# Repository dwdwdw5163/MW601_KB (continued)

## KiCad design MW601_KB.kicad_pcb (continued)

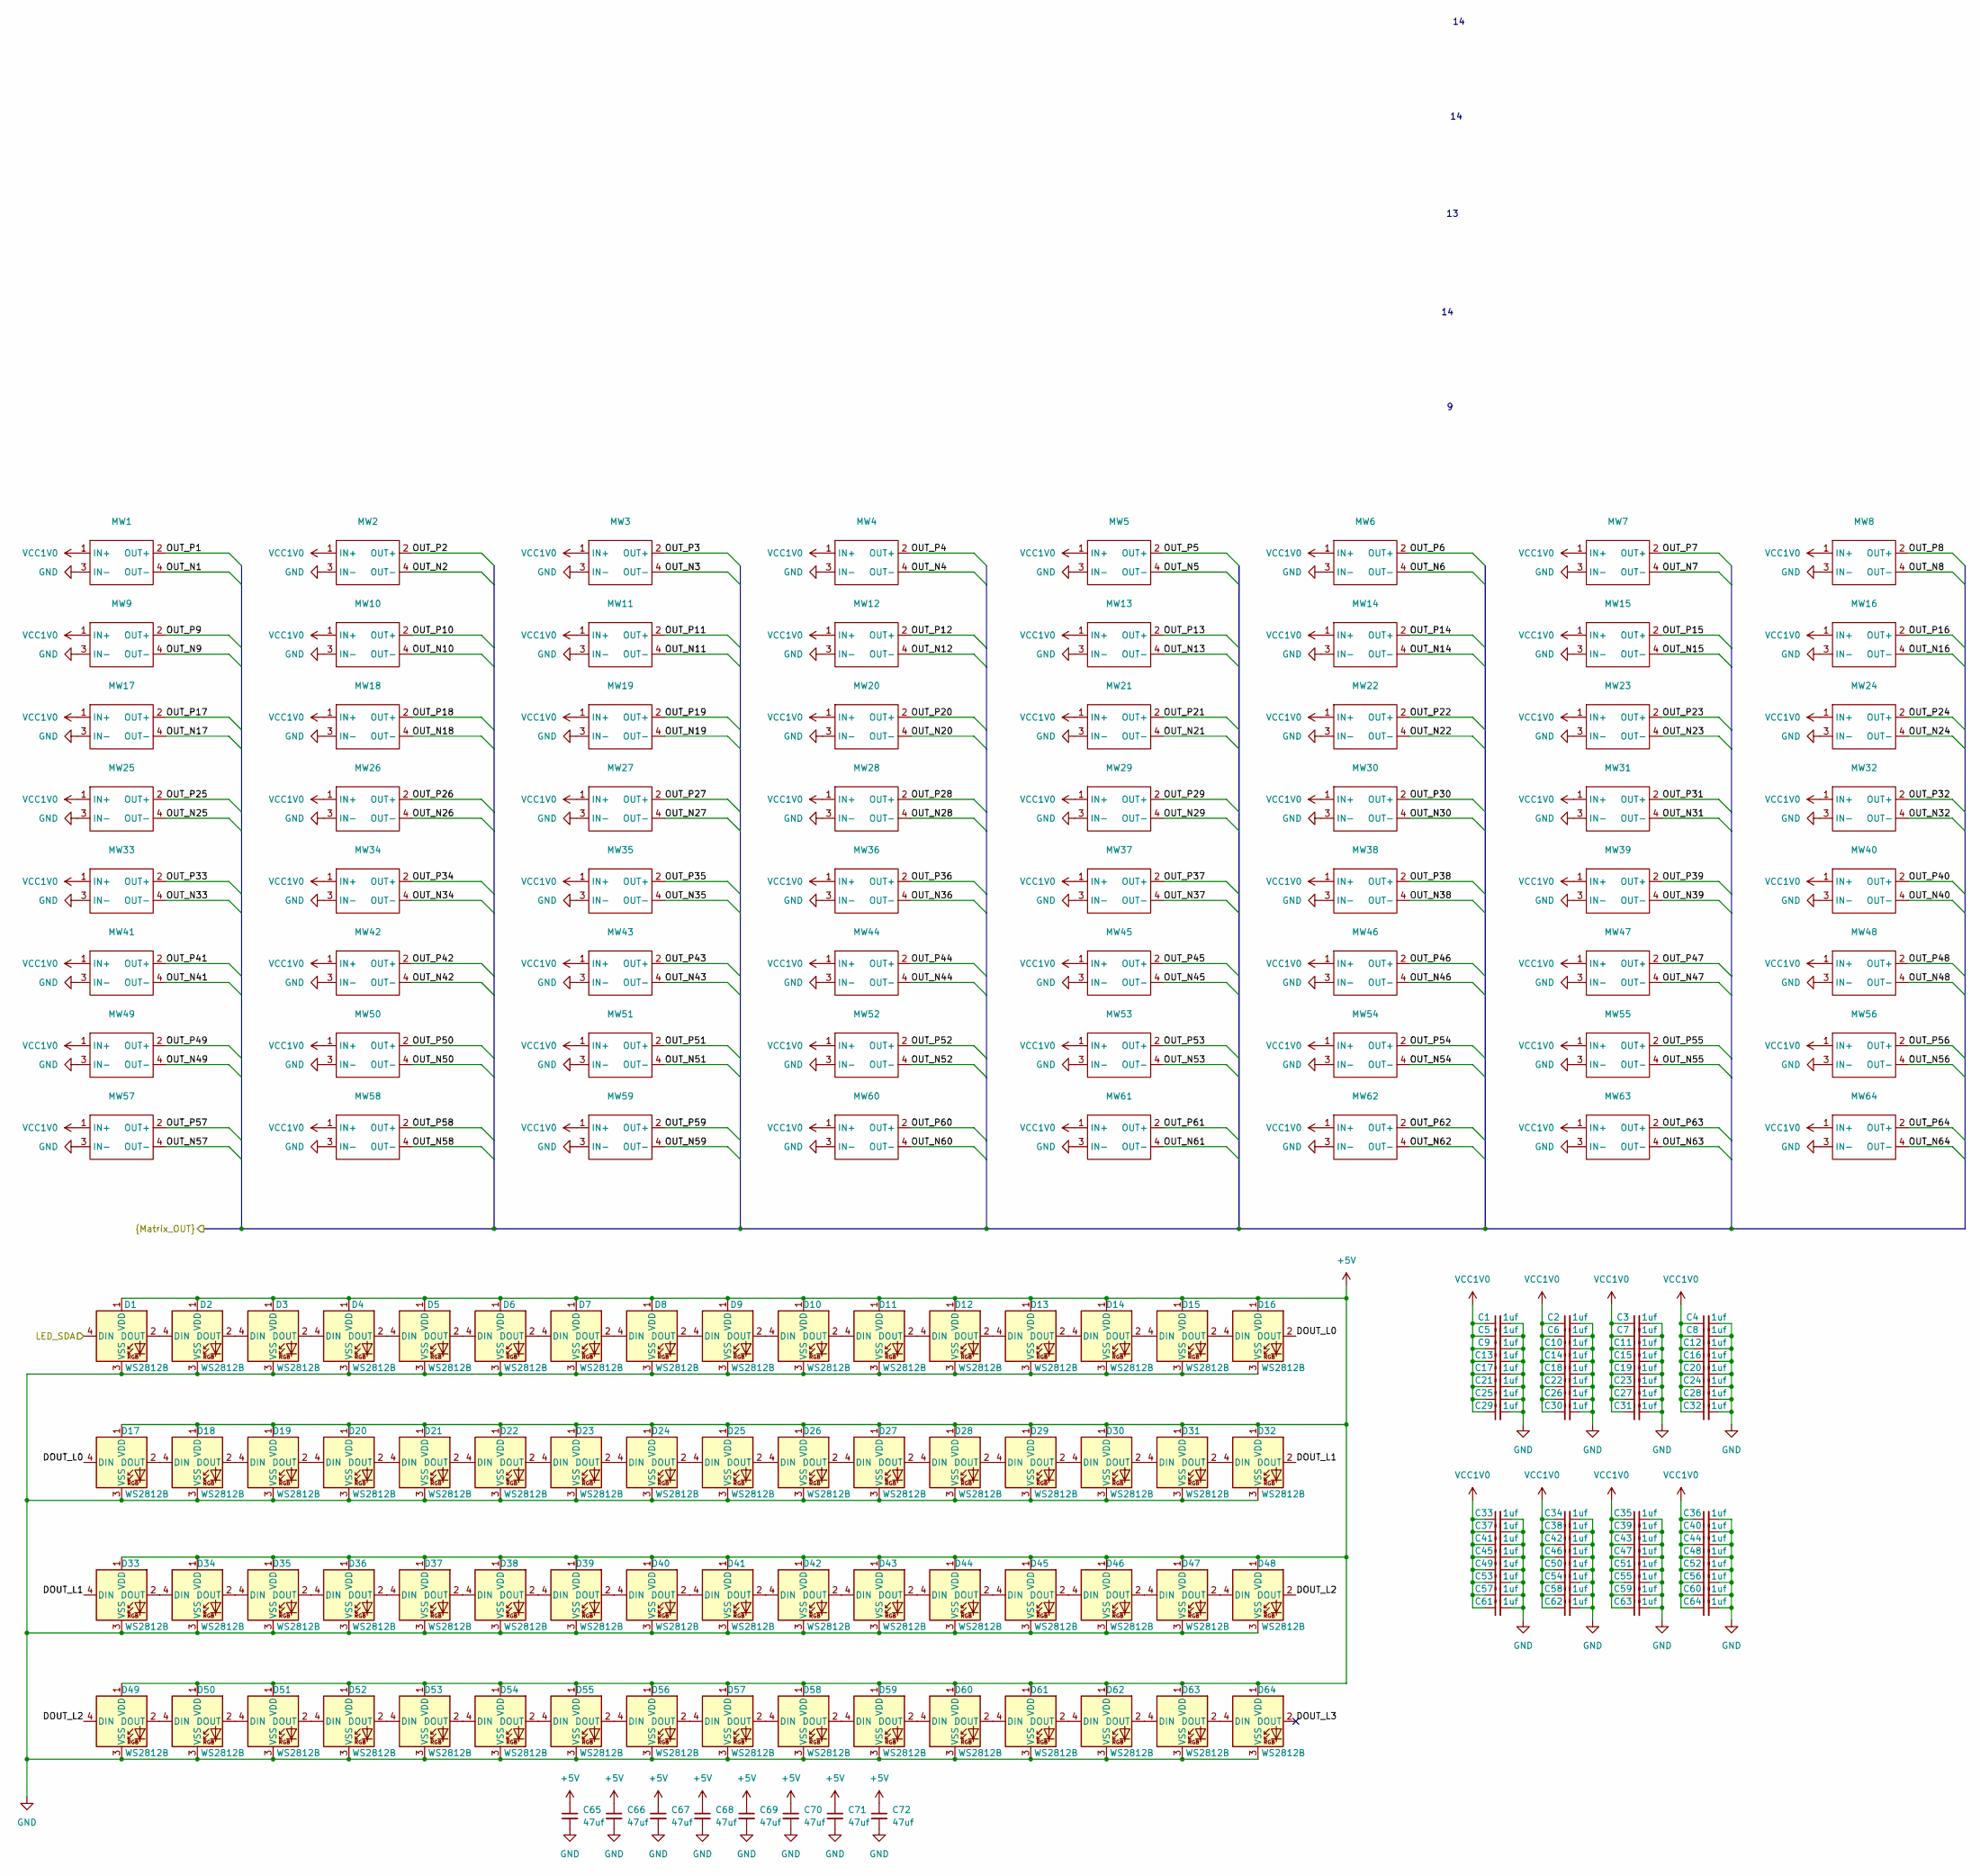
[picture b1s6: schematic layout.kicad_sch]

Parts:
C1, C2, C3, C4, C5, C6, C7, C8, C9, C10, C11, C12, C13, C14, C15, C16, C17, C18, C19, C20, C21, C22, C23, C24, C25, C26, C27, C28, C29, C30, C31, C32, C33, C34, C35, C36, C37, C38, C39, C40, C41, C42, C43, C44, C45, C46, C47, C48, C49, C50, C51, C52, C53, C54, C55, C56, C57, C58, C59, C60, C61, C62, C63, C64: 1uf; C_0603_1608Metric
C65, C66, C67, C68, C69, C70, C71, C72: 47uf; C_0805_2012Metric
D1, D2, D3, D4, D5, D6, D7, D8, D9, D10, D11, D12, D13, D14, D15, D16, D17, D18, D19, D20, D21, D22, D23, D24, D25, D26, D27, D28, D29, D30, D31, D32, D33, D34, D35, D36, D37, D38, D39, D40, D41, D42, D43, D44, D45, D46, D47, D48, D49, D50, D51, D52, D53, D54, D55, D56, D57, D58, D59, D60, D61, D62, D63, D64: WS2812B; WS2812B反贴
MW1, MW2, MW3, MW4, MW5, MW6, MW7, MW8, MW9, MW10, MW11, MW12, MW13, MW14, MW15, MW16, MW17, MW18, MW19, MW20, MW21, MW22, MW23, MW24, MW25, MW26, MW27, MW28, MW29, MW30, MW31, MW32, MW33, MW34, MW35, MW36, MW37, MW38, MW39, MW40, MW41, MW42, MW43, MW44, MW45, MW46, MW47, MW48, MW49, MW50, MW51, MW52, MW53, MW54, MW55, MW56, MW57, MW58, MW59, MW60, MW61, MW62, MW63, MW64: SW_MW601_1.00u

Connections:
+5V: C65.1, C66.1, C67.1, C68.1, C69.1, C70.1, C71.1, C72.1, D1.1 (VDD), D2.1 (VDD), D3.1 (VDD), D4.1 (VDD), D5.1 (VDD), D6.1 (VDD), D7.1 (VDD), D8.1 (VDD), D9.1 (VDD), D10.1 (VDD), D11.1 (VDD), D12.1 (VDD), D13.1 (VDD), D14.1 (VDD), D15.1 (VDD), D16.1 (VDD), D17.1 (VDD), D18.1 (VDD), D19.1 (VDD), D20.1 (VDD), D21.1 (VDD), D22.1 (VDD), D23.1 (VDD), D24.1 (VDD), D25.1 (VDD), D26.1 (VDD), D27.1 (VDD), D28.1 (VDD), D29.1 (VDD), D30.1 (VDD), D31.1 (VDD), D32.1 (VDD), D33.1 (VDD), D34.1 (VDD), D35.1 (VDD), D36.1 (VDD), D37.1 (VDD), D38.1 (VDD), D39.1 (VDD), D40.1 (VDD), D41.1 (VDD), D42.1 (VDD), D43.1 (VDD), D44.1 (VDD), D45.1 (VDD), D46.1 (VDD), D47.1 (VDD), D48.1 (VDD), D49.1 (VDD), D50.1 (VDD), D51.1 (VDD), D52.1 (VDD), D53.1 (VDD), D54.1 (VDD), D55.1 (VDD), D56.1 (VDD), D57.1 (VDD), D58.1 (VDD), D59.1 (VDD), D60.1 (VDD), D61.1 (VDD), D62.1 (VDD), D63.1 (VDD), D64.1 (VDD); also elsewhere on the board
/Key Layout/DOUT_L0: D16.2 (DOUT), D17.4 (DIN)
/Key Layout/DOUT_L1: D32.2 (DOUT), D33.4 (DIN)
/Key Layout/DOUT_L2: D48.2 (DOUT), D49.4 (DIN)
/Key Layout/DOUT_L3: D64.2 (DOUT)
/Key Layout/LED_SDA: D1.4 (DIN); also elsewhere on the board
/Key Layout/OUT_N1: MW1.4 (OUT-); also elsewhere on the board
/Key Layout/OUT_N2: MW2.4 (OUT-); also elsewhere on the board
/Key Layout/OUT_N3: MW3.4 (OUT-); also elsewhere on the board
/Key Layout/OUT_N4: MW4.4 (OUT-); also elsewhere on the board
/Key Layout/OUT_N5: MW5.4 (OUT-); also elsewhere on the board
/Key Layout/OUT_N6: MW6.4 (OUT-); also elsewhere on the board
/Key Layout/OUT_N7: MW7.4 (OUT-); also elsewhere on the board
/Key Layout/OUT_N8: MW8.4 (OUT-); also elsewhere on the board
/Key Layout/OUT_N9: MW9.4 (OUT-); also elsewhere on the board
/Key Layout/OUT_N10: MW10.4 (OUT-); also elsewhere on the board
/Key Layout/OUT_N11: MW11.4 (OUT-); also elsewhere on the board
/Key Layout/OUT_N12: MW12.4 (OUT-); also elsewhere on the board
/Key Layout/OUT_N13: MW13.4 (OUT-); also elsewhere on the board
/Key Layout/OUT_N14: MW14.4 (OUT-); also elsewhere on the board
/Key Layout/OUT_N15: MW15.4 (OUT-); also elsewhere on the board
/Key Layout/OUT_N16: MW16.4 (OUT-); also elsewhere on the board
/Key Layout/OUT_N17: MW17.4 (OUT-); also elsewhere on the board
/Key Layout/OUT_N18: MW18.4 (OUT-); also elsewhere on the board
/Key Layout/OUT_N19: MW19.4 (OUT-); also elsewhere on the board
/Key Layout/OUT_N20: MW20.4 (OUT-); also elsewhere on the board
/Key Layout/OUT_N21: MW21.4 (OUT-); also elsewhere on the board
/Key Layout/OUT_N22: MW22.4 (OUT-); also elsewhere on the board
/Key Layout/OUT_N23: MW23.4 (OUT-); also elsewhere on the board
/Key Layout/OUT_N24: MW24.4 (OUT-); also elsewhere on the board
/Key Layout/OUT_N25: MW25.4 (OUT-); also elsewhere on the board
/Key Layout/OUT_N26: MW26.4 (OUT-); also elsewhere on the board
/Key Layout/OUT_N27: MW27.4 (OUT-); also elsewhere on the board
/Key Layout/OUT_N28: MW28.4 (OUT-); also elsewhere on the board
/Key Layout/OUT_N29: MW29.4 (OUT-); also elsewhere on the board
/Key Layout/OUT_N30: MW30.4 (OUT-); also elsewhere on the board
/Key Layout/OUT_N31: MW31.4 (OUT-); also elsewhere on the board
/Key Layout/OUT_N32: MW32.4 (OUT-); also elsewhere on the board
/Key Layout/OUT_N33: MW33.4 (OUT-); also elsewhere on the board
/Key Layout/OUT_N34: MW34.4 (OUT-); also elsewhere on the board
/Key Layout/OUT_N35: MW35.4 (OUT-); also elsewhere on the board
/Key Layout/OUT_N36: MW36.4 (OUT-); also elsewhere on the board
/Key Layout/OUT_N37: MW37.4 (OUT-); also elsewhere on the board
/Key Layout/OUT_N38: MW38.4 (OUT-); also elsewhere on the board
/Key Layout/OUT_N39: MW39.4 (OUT-); also elsewhere on the board
/Key Layout/OUT_N40: MW40.4 (OUT-); also elsewhere on the board
/Key Layout/OUT_N41: MW41.4 (OUT-); also elsewhere on the board
/Key Layout/OUT_N42: MW42.4 (OUT-); also elsewhere on the board
/Key Layout/OUT_N43: MW43.4 (OUT-); also elsewhere on the board
/Key Layout/OUT_N44: MW44.4 (OUT-); also elsewhere on the board
/Key Layout/OUT_N45: MW45.4 (OUT-); also elsewhere on the board
/Key Layout/OUT_N46: MW46.4 (OUT-); also elsewhere on the board
/Key Layout/OUT_N47: MW47.4 (OUT-); also elsewhere on the board
/Key Layout/OUT_N48: MW48.4 (OUT-); also elsewhere on the board
/Key Layout/OUT_N49: MW49.4 (OUT-); also elsewhere on the board
/Key Layout/OUT_N50: MW50.4 (OUT-); also elsewhere on the board
/Key Layout/OUT_N51: MW51.4 (OUT-); also elsewhere on the board
/Key Layout/OUT_N52: MW52.4 (OUT-); also elsewhere on the board
/Key Layout/OUT_N53: MW53.4 (OUT-); also elsewhere on the board
/Key Layout/OUT_N54: MW54.4 (OUT-); also elsewhere on the board
/Key Layout/OUT_N55: MW55.4 (OUT-); also elsewhere on the board
/Key Layout/OUT_N56: MW56.4 (OUT-); also elsewhere on the board
/Key Layout/OUT_N57: MW57.4 (OUT-); also elsewhere on the board
/Key Layout/OUT_N58: MW58.4 (OUT-); also elsewhere on the board
/Key Layout/OUT_N59: MW59.4 (OUT-); also elsewhere on the board
/Key Layout/OUT_N60: MW60.4 (OUT-); also elsewhere on the board
/Key Layout/OUT_N61: MW61.4 (OUT-); also elsewhere on the board
/Key Layout/OUT_N62: MW62.4 (OUT-); also elsewhere on the board
/Key Layout/OUT_N63: MW63.4 (OUT-); also elsewhere on the board
/Key Layout/OUT_N64: MW64.4 (OUT-); also elsewhere on the board
/Key Layout/OUT_P1: MW1.2 (OUT+); also elsewhere on the board
/Key Layout/OUT_P2: MW2.2 (OUT+); also elsewhere on the board
/Key Layout/OUT_P3: MW3.2 (OUT+); also elsewhere on the board
/Key Layout/OUT_P4: MW4.2 (OUT+); also elsewhere on the board
/Key Layout/OUT_P5: MW5.2 (OUT+); also elsewhere on the board
/Key Layout/OUT_P6: MW6.2 (OUT+); also elsewhere on the board
/Key Layout/OUT_P7: MW7.2 (OUT+); also elsewhere on the board
/Key Layout/OUT_P8: MW8.2 (OUT+); also elsewhere on the board
/Key Layout/OUT_P9: MW9.2 (OUT+); also elsewhere on the board
/Key Layout/OUT_P10: MW10.2 (OUT+); also elsewhere on the board
/Key Layout/OUT_P11: MW11.2 (OUT+); also elsewhere on the board
/Key Layout/OUT_P12: MW12.2 (OUT+); also elsewhere on the board
/Key Layout/OUT_P13: MW13.2 (OUT+); also elsewhere on the board
/Key Layout/OUT_P14: MW14.2 (OUT+); also elsewhere on the board
/Key Layout/OUT_P15: MW15.2 (OUT+); also elsewhere on the board
/Key Layout/OUT_P16: MW16.2 (OUT+); also elsewhere on the board
/Key Layout/OUT_P17: MW17.2 (OUT+); also elsewhere on the board
/Key Layout/OUT_P18: MW18.2 (OUT+); also elsewhere on the board
/Key Layout/OUT_P19: MW19.2 (OUT+); also elsewhere on the board
/Key Layout/OUT_P20: MW20.2 (OUT+); also elsewhere on the board
/Key Layout/OUT_P21: MW21.2 (OUT+); also elsewhere on the board
/Key Layout/OUT_P22: MW22.2 (OUT+); also elsewhere on the board
/Key Layout/OUT_P23: MW23.2 (OUT+); also elsewhere on the board
/Key Layout/OUT_P24: MW24.2 (OUT+); also elsewhere on the board
/Key Layout/OUT_P25: MW25.2 (OUT+); also elsewhere on the board
/Key Layout/OUT_P26: MW26.2 (OUT+); also elsewhere on the board
/Key Layout/OUT_P27: MW27.2 (OUT+); also elsewhere on the board
/Key Layout/OUT_P28: MW28.2 (OUT+); also elsewhere on the board
/Key Layout/OUT_P29: MW29.2 (OUT+); also elsewhere on the board
/Key Layout/OUT_P30: MW30.2 (OUT+); also elsewhere on the board
/Key Layout/OUT_P31: MW31.2 (OUT+); also elsewhere on the board
/Key Layout/OUT_P32: MW32.2 (OUT+); also elsewhere on the board
/Key Layout/OUT_P33: MW33.2 (OUT+); also elsewhere on the board
/Key Layout/OUT_P34: MW34.2 (OUT+); also elsewhere on the board
/Key Layout/OUT_P35: MW35.2 (OUT+); also elsewhere on the board
/Key Layout/OUT_P36: MW36.2 (OUT+); also elsewhere on the board
/Key Layout/OUT_P37: MW37.2 (OUT+); also elsewhere on the board
/Key Layout/OUT_P38: MW38.2 (OUT+); also elsewhere on the board
/Key Layout/OUT_P39: MW39.2 (OUT+); also elsewhere on the board
/Key Layout/OUT_P40: MW40.2 (OUT+); also elsewhere on the board
/Key Layout/OUT_P41: MW41.2 (OUT+); also elsewhere on the board
/Key Layout/OUT_P42: MW42.2 (OUT+); also elsewhere on the board
/Key Layout/OUT_P43: MW43.2 (OUT+); also elsewhere on the board
/Key Layout/OUT_P44: MW44.2 (OUT+); also elsewhere on the board
/Key Layout/OUT_P45: MW45.2 (OUT+); also elsewhere on the board
/Key Layout/OUT_P46: MW46.2 (OUT+); also elsewhere on the board
/Key Layout/OUT_P47: MW47.2 (OUT+); also elsewhere on the board
/Key Layout/OUT_P48: MW48.2 (OUT+); also elsewhere on the board
/Key Layout/OUT_P49: MW49.2 (OUT+); also elsewhere on the board
/Key Layout/OUT_P50: MW50.2 (OUT+); also elsewhere on the board
/Key Layout/OUT_P51: MW51.2 (OUT+); also elsewhere on the board
/Key Layout/OUT_P52: MW52.2 (OUT+); also elsewhere on the board
/Key Layout/OUT_P53: MW53.2 (OUT+); also elsewhere on the board
/Key Layout/OUT_P54: MW54.2 (OUT+); also elsewhere on the board
/Key Layout/OUT_P55: MW55.2 (OUT+); also elsewhere on the board
/Key Layout/OUT_P56: MW56.2 (OUT+); also elsewhere on the board
/Key Layout/OUT_P57: MW57.2 (OUT+); also elsewhere on the board
/Key Layout/OUT_P58: MW58.2 (OUT+); also elsewhere on the board
/Key Layout/OUT_P59: MW59.2 (OUT+); also elsewhere on the board
/Key Layout/OUT_P60: MW60.2 (OUT+); also elsewhere on the board
/Key Layout/OUT_P61: MW61.2 (OUT+); also elsewhere on the board
/Key Layout/OUT_P62: MW62.2 (OUT+); also elsewhere on the board
/Key Layout/OUT_P63: MW63.2 (OUT+); also elsewhere on the board
/Key Layout/OUT_P64: MW64.2 (OUT+); also elsewhere on the board
GND: C1.2, C2.2, C3.2, C4.2, C5.2, C6.2, C7.2, C8.2, C9.2, C10.2, C11.2, C12.2, C13.2, C14.2, C15.2, C16.2, C17.2, C18.2, C19.2, C20.2, C21.2, C22.2, C23.2, C24.2, C25.2, C26.2, C27.2, C28.2, C29.2, C30.2, C31.2, C32.2, C33.2, C34.2, C35.2, C36.2, C37.2, C38.2, C39.2, C40.2, C41.2, C42.2, C43.2, C44.2, C45.2, C46.2, C47.2, C48.2, C49.2, C50.2, C51.2, C52.2, C53.2, C54.2, C55.2, C56.2, C57.2, C58.2, C59.2, C60.2, C61.2, C62.2, C63.2, C64.2, C65.2, C66.2, C67.2, C68.2, C69.2, C70.2, C71.2, C72.2, D1.3 (VSS), D2.3 (VSS), D3.3 (VSS), D4.3 (VSS), D5.3 (VSS), D6.3 (VSS), D7.3 (VSS), D8.3 (VSS), D9.3 (VSS), D10.3 (VSS), D11.3 (VSS), D12.3 (VSS), D13.3 (VSS), D14.3 (VSS), D15.3 (VSS), D16.3 (VSS), D17.3 (VSS), D18.3 (VSS), D19.3 (VSS), D20.3 (VSS), D21.3 (VSS), D22.3 (VSS), D23.3 (VSS), D24.3 (VSS), D25.3 (VSS), D26.3 (VSS), D27.3 (VSS), D28.3 (VSS), D29.3 (VSS), D30.3 (VSS), D31.3 (VSS), D32.3 (VSS), D33.3 (VSS), D34.3 (VSS), D35.3 (VSS), D36.3 (VSS), D37.3 (VSS), D38.3 (VSS), D39.3 (VSS), D40.3 (VSS), D41.3 (VSS), D42.3 (VSS), D43.3 (VSS), D44.3 (VSS), D45.3 (VSS), D46.3 (VSS), D47.3 (VSS), D48.3 (VSS), D49.3 (VSS), D50.3 (VSS), D51.3 (VSS), D52.3 (VSS), D53.3 (VSS), D54.3 (VSS), D55.3 (VSS), D56.3 (VSS), D57.3 (VSS), D58.3 (VSS), D59.3 (VSS), D60.3 (VSS), D61.3 (VSS), D62.3 (VSS), D63.3 (VSS), D64.3 (VSS), MW1.3 (IN-), MW2.3 (IN-), MW3.3 (IN-), MW4.3 (IN-), MW5.3 (IN-), MW6.3 (IN-), MW7.3 (IN-), MW8.3 (IN-), MW9.3 (IN-), MW10.3 (IN-), MW11.3 (IN-), MW12.3 (IN-), MW13.3 (IN-), MW14.3 (IN-), MW15.3 (IN-), MW16.3 (IN-), MW17.3 (IN-), MW18.3 (IN-), MW19.3 (IN-), MW20.3 (IN-), MW21.3 (IN-), MW22.3 (IN-), MW23.3 (IN-), MW24.3 (IN-), MW25.3 (IN-), MW26.3 (IN-), MW27.3 (IN-), MW28.3 (IN-), MW29.3 (IN-), MW30.3 (IN-), MW31.3 (IN-), MW32.3 (IN-), MW33.3 (IN-), MW34.3 (IN-), MW35.3 (IN-), MW36.3 (IN-), MW37.3 (IN-), MW38.3 (IN-), MW39.3 (IN-), MW40.3 (IN-), MW41.3 (IN-), MW42.3 (IN-), MW43.3 (IN-), MW44.3 (IN-), MW45.3 (IN-), MW46.3 (IN-), MW47.3 (IN-), MW48.3 (IN-), MW49.3 (IN-), MW50.3 (IN-), MW51.3 (IN-), MW52.3 (IN-), MW53.3 (IN-), MW54.3 (IN-), MW55.3 (IN-), MW56.3 (IN-), MW57.3 (IN-), MW58.3 (IN-), MW59.3 (IN-), MW60.3 (IN-), MW61.3 (IN-), MW62.3 (IN-), MW63.3 (IN-), MW64.3 (IN-); also elsewhere on the board
unnamed: D1.2 (DOUT), D2.4 (DIN)
unnamed: D2.2 (DOUT), D3.4 (DIN)
unnamed: D3.2 (DOUT), D4.4 (DIN)
unnamed: D4.2 (DOUT), D5.4 (DIN)
unnamed: D5.2 (DOUT), D6.4 (DIN)
unnamed: D6.2 (DOUT), D7.4 (DIN)
unnamed: D7.2 (DOUT), D8.4 (DIN)
unnamed: D8.2 (DOUT), D9.4 (DIN)
unnamed: D9.2 (DOUT), D10.4 (DIN)
unnamed: D10.2 (DOUT), D11.4 (DIN)
unnamed: D11.2 (DOUT), D12.4 (DIN)
unnamed: D12.2 (DOUT), D13.4 (DIN)
unnamed: D13.2 (DOUT), D14.4 (DIN)
unnamed: D14.2 (DOUT), D15.4 (DIN)
unnamed: D15.2 (DOUT), D16.4 (DIN)
unnamed: D17.2 (DOUT), D18.4 (DIN)
unnamed: D18.2 (DOUT), D19.4 (DIN)
unnamed: D19.2 (DOUT), D20.4 (DIN)
unnamed: D20.2 (DOUT), D21.4 (DIN)
unnamed: D21.2 (DOUT), D22.4 (DIN)
unnamed: D22.2 (DOUT), D23.4 (DIN)
unnamed: D23.2 (DOUT), D24.4 (DIN)
unnamed: D24.2 (DOUT), D25.4 (DIN)
unnamed: D25.2 (DOUT), D26.4 (DIN)
unnamed: D26.2 (DOUT), D27.4 (DIN)
unnamed: D27.2 (DOUT), D28.4 (DIN)
unnamed: D28.2 (DOUT), D29.4 (DIN)
unnamed: D29.2 (DOUT), D30.4 (DIN)
unnamed: D30.2 (DOUT), D31.4 (DIN)
unnamed: D31.2 (DOUT), D32.4 (DIN)
unnamed: D33.2 (DOUT), D34.4 (DIN)
unnamed: D34.2 (DOUT), D35.4 (DIN)
unnamed: D35.2 (DOUT), D36.4 (DIN)
unnamed: D36.2 (DOUT), D37.4 (DIN)
unnamed: D37.2 (DOUT), D38.4 (DIN)
unnamed: D38.2 (DOUT), D39.4 (DIN)
unnamed: D39.2 (DOUT), D40.4 (DIN)
unnamed: D40.2 (DOUT), D41.4 (DIN)
unnamed: D41.2 (DOUT), D42.4 (DIN)
unnamed: D42.2 (DOUT), D43.4 (DIN)
unnamed: D43.2 (DOUT), D44.4 (DIN)
unnamed: D44.2 (DOUT), D45.4 (DIN)
unnamed: D45.2 (DOUT), D46.4 (DIN)
unnamed: D46.2 (DOUT), D47.4 (DIN)
unnamed: D47.2 (DOUT), D48.4 (DIN)
unnamed: D49.2 (DOUT), D50.4 (DIN)
unnamed: D50.2 (DOUT), D51.4 (DIN)
unnamed: D51.2 (DOUT), D52.4 (DIN)
unnamed: D52.2 (DOUT), D53.4 (DIN)
unnamed: D53.2 (DOUT), D54.4 (DIN)
unnamed: D54.2 (DOUT), D55.4 (DIN)
unnamed: D55.2 (DOUT), D56.4 (DIN)
unnamed: D56.2 (DOUT), D57.4 (DIN)
unnamed: D57.2 (DOUT), D58.4 (DIN)
unnamed: D58.2 (DOUT), D59.4 (DIN)
unnamed: D59.2 (DOUT), D60.4 (DIN)
unnamed: D60.2 (DOUT), D61.4 (DIN)
unnamed: D61.2 (DOUT), D62.4 (DIN)
unnamed: D62.2 (DOUT), D63.4 (DIN)
unnamed: D63.2 (DOUT), D64.4 (DIN)
VCC1V0: C1.1, C2.1, C3.1, C4.1, C5.1, C6.1, C7.1, C8.1, C9.1, C10.1, C11.1, C12.1, C13.1, C14.1, C15.1, C16.1, C17.1, C18.1, C19.1, C20.1, C21.1, C22.1, C23.1, C24.1, C25.1, C26.1, C27.1, C28.1, C29.1, C30.1, C31.1, C32.1, C33.1, C34.1, C35.1, C36.1, C37.1, C38.1, C39.1, C40.1, C41.1, C42.1, C43.1, C44.1, C45.1, C46.1, C47.1, C48.1, C49.1, C50.1, C51.1, C52.1, C53.1, C54.1, C55.1, C56.1, C57.1, C58.1, C59.1, C60.1, C61.1, C62.1, C63.1, C64.1, MW1.1 (IN+), MW2.1 (IN+), MW3.1 (IN+), MW4.1 (IN+), MW5.1 (IN+), MW6.1 (IN+), MW7.1 (IN+), MW8.1 (IN+), MW9.1 (IN+), MW10.1 (IN+), MW11.1 (IN+), MW12.1 (IN+), MW13.1 (IN+), MW14.1 (IN+), MW15.1 (IN+), MW16.1 (IN+), MW17.1 (IN+), MW18.1 (IN+), MW19.1 (IN+), MW20.1 (IN+), MW21.1 (IN+), MW22.1 (IN+), MW23.1 (IN+), MW24.1 (IN+), MW25.1 (IN+), MW26.1 (IN+), MW27.1 (IN+), MW28.1 (IN+), MW29.1 (IN+), MW30.1 (IN+), MW31.1 (IN+), MW32.1 (IN+), MW33.1 (IN+), MW34.1 (IN+), MW35.1 (IN+), MW36.1 (IN+), MW37.1 (IN+), MW38.1 (IN+), MW39.1 (IN+), MW40.1 (IN+), MW41.1 (IN+), MW42.1 (IN+), MW43.1 (IN+), MW44.1 (IN+), MW45.1 (IN+), MW46.1 (IN+), MW47.1 (IN+), MW48.1 (IN+), MW49.1 (IN+), MW50.1 (IN+), MW51.1 (IN+), MW52.1 (IN+), MW53.1 (IN+), MW54.1 (IN+), MW55.1 (IN+), MW56.1 (IN+), MW57.1 (IN+), MW58.1 (IN+), MW59.1 (IN+), MW60.1 (IN+), MW61.1 (IN+), MW62.1 (IN+), MW63.1 (IN+), MW64.1 (IN+); also elsewhere on the board

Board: 4 copper layers, 319 parts (310 on the bottom side), 268 nets, no tracks yet.

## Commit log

2024-08-16 add cap
2024-09-15 solder
